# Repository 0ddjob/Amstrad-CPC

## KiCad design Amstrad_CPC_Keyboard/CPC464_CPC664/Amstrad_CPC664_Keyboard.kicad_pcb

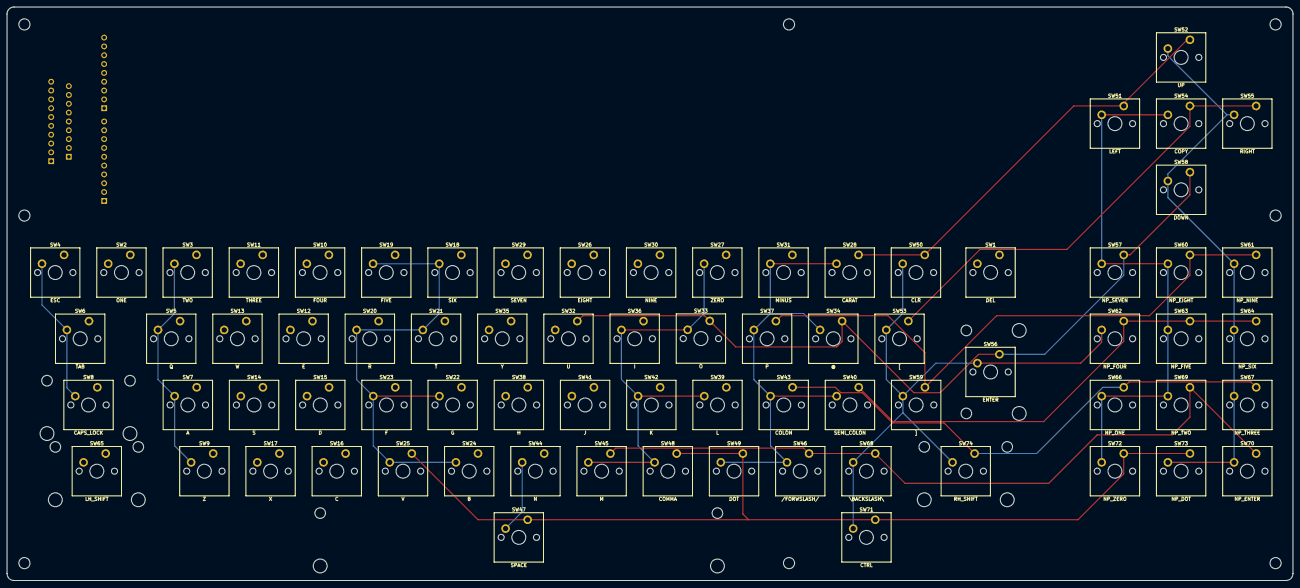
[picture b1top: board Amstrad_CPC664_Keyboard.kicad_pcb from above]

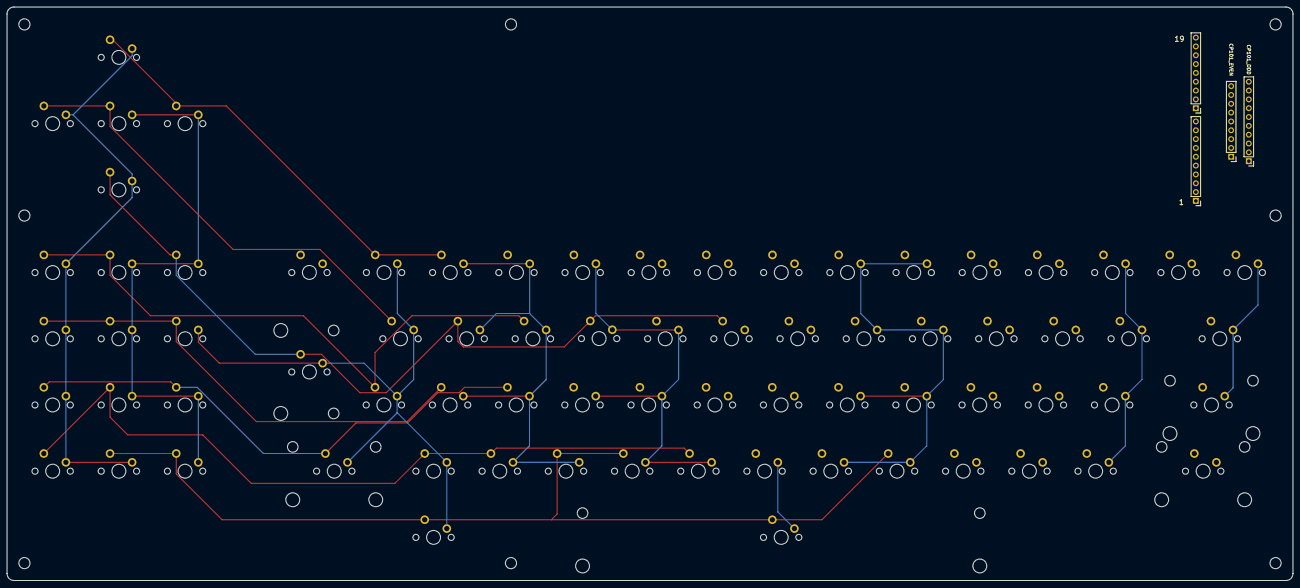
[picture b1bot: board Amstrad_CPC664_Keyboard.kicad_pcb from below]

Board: 2 copper layers, 370.0 x 165.0 mm, 91 parts (4 on the bottom side), 19 nets.

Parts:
H1, H2, H3, H4, H5, H6, H7, H8: MountingHole; MountingHole_3.2mm_M3
J1: CP101_ODD; PinHeader_1x10_P2.54mm_Vertical
J2: CP101_EVEN; PinHeader_1x09_P2.54mm_Vertical
J3: CP102_A; PinHeader_1x10_P2.54mm_Vertical
J4: CP102_B; PinHeader_1x09_P2.54mm_Vertical
KB8: CAPS_LOCK; Stabilizer_Cherry_MX_2.00u
KB47: SPACE; Stabilizer_Cherry_MX_7.00u
KB56: ENTER; Stabilizer_Cherry_MX_2.00u
KB65: LH_SHIFT; Stabilizer_Cherry_MX_2.00u
KB74: RH_SHIFT; Stabilizer_Cherry_MX_2.00u
SW1: DEL; SW_Cherry_MX_PCB_1.25u
SW2: ONE; SW_Cherry_MX_PCB_1.00u
SW3: TWO; SW_Cherry_MX_PCB_1.00u
SW4: ESC; SW_Cherry_MX_PCB_1.00u
SW5: Q; SW_Cherry_MX_PCB_1.00u
SW6: TAB; SW_Cherry_MX_PCB_1.75u
SW7: A; SW_Cherry_MX_PCB_1.00u
SW8: CAPS_LOCK; SW_Cherry_MX_PCB_2.00u
SW9: Z; SW_Cherry_MX_PCB_1.00u
SW10: FOUR; SW_Cherry_MX_PCB_1.00u
SW11: THREE; SW_Cherry_MX_PCB_1.00u
SW12: E; SW_Cherry_MX_PCB_1.00u
SW13: W; SW_Cherry_MX_PCB_1.00u
SW14: S; SW_Cherry_MX_PCB_1.00u
SW15: D; SW_Cherry_MX_PCB_1.00u
SW16: C; SW_Cherry_MX_PCB_1.00u
SW17: X; SW_Cherry_MX_PCB_1.00u
SW18: SIX; SW_Cherry_MX_PCB_1.00u
SW19: FIVE; SW_Cherry_MX_PCB_1.00u
SW20: R; SW_Cherry_MX_PCB_1.00u
SW21: T; SW_Cherry_MX_PCB_1.00u
SW22: G; SW_Cherry_MX_PCB_1.00u
SW23: F; SW_Cherry_MX_PCB_1.00u
SW24: B; SW_Cherry_MX_PCB_1.00u
SW25: V; SW_Cherry_MX_PCB_1.00u
SW26: EIGHT; SW_Cherry_MX_PCB_1.00u
SW27: ZERO; SW_Cherry_MX_PCB_1.00u
SW28: CARAT; SW_Cherry_MX_PCB_1.00u
SW29: SEVEN; SW_Cherry_MX_PCB_1.00u
SW30: NINE; SW_Cherry_MX_PCB_1.00u
SW31: MINUS; SW_Cherry_MX_PCB_1.00u
SW32: U; SW_Cherry_MX_PCB_1.00u
SW33: O; SW_Cherry_MX_PCB_1.00u
SW34: @; SW_Cherry_MX_PCB_1.00u
SW35: Y; SW_Cherry_MX_PCB_1.00u
SW36: I; SW_Cherry_MX_PCB_1.00u
SW37: P; SW_Cherry_MX_PCB_1.00u
SW38: H; SW_Cherry_MX_PCB_1.00u
SW39: L; SW_Cherry_MX_PCB_1.00u
SW40: SEMI_COLON; SW_Cherry_MX_PCB_1.00u
SW41: J; SW_Cherry_MX_PCB_1.00u
SW42: K; SW_Cherry_MX_PCB_1.00u
SW43: COLON; SW_Cherry_MX_PCB_1.00u
SW44: N; SW_Cherry_MX_PCB_1.00u
SW45: M; SW_Cherry_MX_PCB_1.00u
SW46: /FORWSLASH/; SW_Cherry_MX_PCB_1.00u
SW47: SPACE; SW_Cherry_MX_PCB_7.00u
SW48: COMMA; SW_Cherry_MX_PCB_1.00u
SW49: DOT; SW_Cherry_MX_PCB_1.00u
SW50: CLR; SW_Cherry_MX_PCB_1.00u
SW51: LEFT; SW_Cherry_MX_PCB_1.00u
SW52: UP; SW_Cherry_MX_PCB_1.00u
SW53: [; SW_Cherry_MX_PCB_1.00u
SW54: COPY; SW_Cherry_MX_PCB_1.00u
SW55: RIGHT; SW_Cherry_MX_PCB_1.00u
SW56: ENTER; SW_Cherry_MX_PCB_ISOEnter
SW57: NP_SEVEN; SW_Cherry_MX_PCB_1.00u
SW58: DOWN; SW_Cherry_MX_PCB_1.00u
SW59: ]; SW_Cherry_MX_PCB_1.00u
SW60: NP_EIGHT; SW_Cherry_MX_PCB_1.00u
SW61: NP_NINE; SW_Cherry_MX_PCB_1.00u
SW62: NP_FOUR; SW_Cherry_MX_PCB_1.00u
SW63: NP_FIVE; SW_Cherry_MX_PCB_1.00u
SW64: NP_SIX; SW_Cherry_MX_PCB_1.00u
SW65: LH_SHIFT; SW_Cherry_MX_PCB_2.25u
SW66: NP_ONE; SW_Cherry_MX_PCB_1.00u
SW67: NP_THREE; SW_Cherry_MX_PCB_1.00u
SW68: \BACKSLASH\; SW_Cherry_MX_PCB_1.00u
SW69: NP_TWO; SW_Cherry_MX_PCB_1.00u
SW70: NP_ENTER; SW_Cherry_MX_PCB_1.00u
SW71: CTRL; SW_Cherry_MX_PCB_1.00u
SW72: NP_ZERO; SW_Cherry_MX_PCB_1.00u
SW73: NP_DOT; SW_Cherry_MX_PCB_1.00u
SW74: RH_SHIFT; SW_Cherry_MX_PCB_2.00u

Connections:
KB_1: J1.1, J3.1, SW1.1
KB_2: J2.1, J3.2, SW1.2
KB_3: J1.2, J3.3, SW2.2, SW10.2, SW18.2, SW26.2, SW27.2, SW28.2, SW50.2, SW51.2, SW52.2
KB_4: J2.2, J3.4, SW3.2, SW11.2, SW19.2, SW29.2, SW30.2, SW31.2, SW53.2, SW54.2, SW55.2
KB_5: J1.3, J3.5, SW4.2, SW12.2, SW20.2, SW32.2, SW33.2, SW34.2, SW56.2, SW57.2, SW58.2
KB_6: J2.3, J3.6, SW5.2, SW13.2, SW21.2, SW35.2, SW36.2, SW37.2, SW59.2, SW60.2, SW61.2
KB_7: J1.4, J3.7, SW6.2, SW14.2, SW22.2, SW38.2, SW39.2, SW40.2, SW62.2, SW63.2, SW64.2
KB_8: J2.4, J3.8, SW7.2, SW15.2, SW23.2, SW41.2, SW42.2, SW43.2, SW65.2, SW66.2, SW67.2, SW74.2
KB_9: J1.5, J3.9, SW8.2, SW16.2, SW24.2, SW44.2, SW45.2, SW46.2, SW68.2, SW69.2, SW70.2
KB_10: J2.5, J3.10, SW9.2, SW17.2, SW25.2, SW47.2, SW48.2, SW49.2, SW71.2, SW72.2, SW73.2
KB_11: J1.6, SW2.1, SW3.1, SW4.1, SW5.1, SW6.1, SW7.1, SW8.1, SW9.1
KB_12: J2.6, SW10.1, SW11.1, SW12.1, SW13.1, SW14.1, SW15.1, SW16.1, SW17.1
KB_13: J1.7, SW18.1, SW19.1, SW20.1, SW21.1, SW22.1, SW23.1, SW24.1, SW25.1
KB_14: J2.7, SW26.1, SW29.1, SW32.1, SW35.1, SW38.1, SW41.1, SW44.1, SW47.1
KB_15: J1.8, SW27.1, SW30.1, SW33.1, SW36.1, SW39.1, SW42.1, SW45.1, SW48.1
KB_16: J2.8, SW28.1, SW31.1, SW34.1, SW37.1, SW40.1, SW43.1, SW46.1, SW49.1
KB_17: J1.9, SW50.1, SW53.1, SW56.1, SW59.1, SW62.1, SW65.1, SW68.1, SW71.1, SW74.1
KB_18: J2.9, SW51.1, SW54.1, SW57.1, SW60.1, SW63.1, SW66.1, SW69.1, SW72.1
KB_19: J1.10, SW52.1, SW55.1, SW58.1, SW61.1, SW64.1, SW67.1, SW70.1, SW73.1

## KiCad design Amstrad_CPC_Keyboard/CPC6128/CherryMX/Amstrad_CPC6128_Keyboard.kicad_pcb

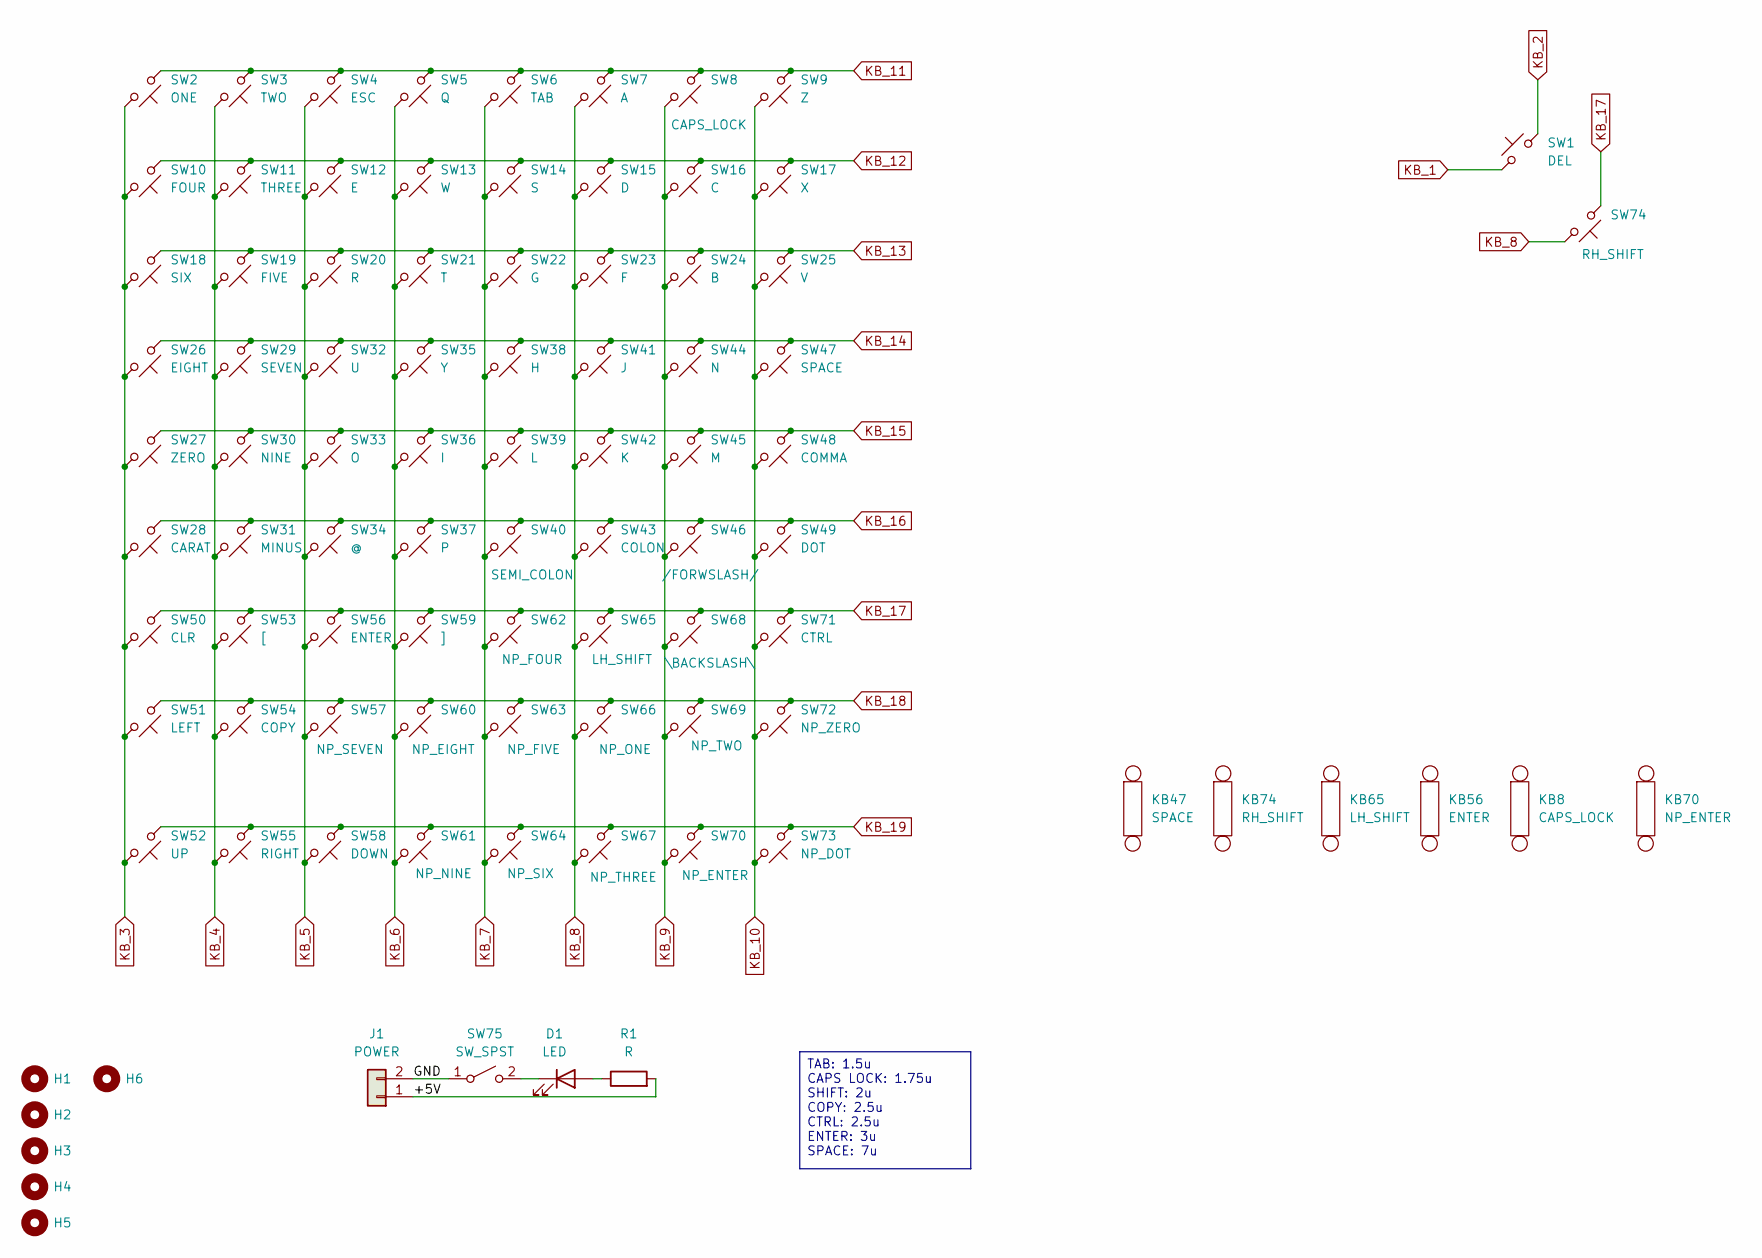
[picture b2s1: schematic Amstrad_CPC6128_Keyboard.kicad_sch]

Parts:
D1: LED; LED_D5.0mm
H1, H2, H3, H4, H5, H6: MountingHole; MountingHole_3.2mm_M3
J1: POWER; PinHeader_1x02_P2.54mm_Vertical
KB8: CAPS_LOCK; Stabilizer_Cherry_MX_2.00u
KB47: SPACE; Stabilizer_Cherry_MX_7.00u
KB56: ENTER; Stabilizer_Cherry_MX_2.00u
KB65: LH_SHIFT; Stabilizer_Cherry_MX_2.00u
KB70: NP_ENTER; Stabilizer_Cherry_MX_3.00u
KB74: RH_SHIFT; Stabilizer_Cherry_MX_2.00u
R1: R; R_Axial_DIN0207_L6.3mm_D2.5mm_P10.16mm_Horizontal
SW1: DEL; SW_Cherry_MX_PCB_1.00u
SW2: ONE; SW_Cherry_MX_PCB_1.00u
SW3: TWO; SW_Cherry_MX_PCB_1.00u
SW4: ESC; SW_Cherry_MX_PCB_1.00u
SW5: Q; SW_Cherry_MX_PCB_1.00u
SW6: TAB; SW_Cherry_MX_PCB_1.50u
SW7: A; SW_Cherry_MX_PCB_1.00u
SW8: CAPS_LOCK; SW_Cherry_MX_PCB_1.75u
SW9: Z; SW_Cherry_MX_PCB_1.00u
SW10: FOUR; SW_Cherry_MX_PCB_1.00u
SW11: THREE; SW_Cherry_MX_PCB_1.00u
SW12: E; SW_Cherry_MX_PCB_1.00u
SW13: W; SW_Cherry_MX_PCB_1.00u
SW14: S; SW_Cherry_MX_PCB_1.00u
SW15: D; SW_Cherry_MX_PCB_1.00u
SW16: C; SW_Cherry_MX_PCB_1.00u
SW17: X; SW_Cherry_MX_PCB_1.00u
SW18: SIX; SW_Cherry_MX_PCB_1.00u
SW19: FIVE; SW_Cherry_MX_PCB_1.00u
SW20: R; SW_Cherry_MX_PCB_1.00u
SW21: T; SW_Cherry_MX_PCB_1.00u
SW22: G; SW_Cherry_MX_PCB_1.00u
SW23: F; SW_Cherry_MX_PCB_1.00u
SW24: B; SW_Cherry_MX_PCB_1.00u
SW25: V; SW_Cherry_MX_PCB_1.00u
SW26: EIGHT; SW_Cherry_MX_PCB_1.00u
SW27: ZERO; SW_Cherry_MX_PCB_1.00u
SW28: CARAT; SW_Cherry_MX_PCB_1.00u
SW29: SEVEN; SW_Cherry_MX_PCB_1.00u
SW30: NINE; SW_Cherry_MX_PCB_1.00u
SW31: MINUS; SW_Cherry_MX_PCB_1.00u
SW32: U; SW_Cherry_MX_PCB_1.00u
SW33: O; SW_Cherry_MX_PCB_1.00u
SW34: @; SW_Cherry_MX_PCB_1.00u
SW35: Y; SW_Cherry_MX_PCB_1.00u
SW36: I; SW_Cherry_MX_PCB_1.00u
SW37: P; SW_Cherry_MX_PCB_1.00u
SW38: H; SW_Cherry_MX_PCB_1.00u
SW39: L; SW_Cherry_MX_PCB_1.00u
SW40: SEMI_COLON; SW_Cherry_MX_PCB_1.00u
SW41: J; SW_Cherry_MX_PCB_1.00u
SW42: K; SW_Cherry_MX_PCB_1.00u
SW43: COLON; SW_Cherry_MX_PCB_1.00u
SW44: N; SW_Cherry_MX_PCB_1.00u
SW45: M; SW_Cherry_MX_PCB_1.00u
SW46: /FORWSLASH/; SW_Cherry_MX_PCB_1.00u
SW47: SPACE; SW_Cherry_MX_PCB_7.00u
SW48: COMMA; SW_Cherry_MX_PCB_1.00u
SW49: DOT; SW_Cherry_MX_PCB_1.00u
SW50: CLR; SW_Cherry_MX_PCB_1.00u
SW51: LEFT; SW_Cherry_MX_PCB_1.00u
SW52: UP; SW_Cherry_MX_PCB_1.00u
SW53: [; SW_Cherry_MX_PCB_1.00u
SW54: COPY; SW_Cherry_MX_PCB_2.50u
SW55: RIGHT; SW_Cherry_MX_PCB_1.00u
SW56: ENTER; SW_Cherry_MX_PCB_ISOEnter
SW57: NP_SEVEN; SW_Cherry_MX_PCB_1.00u
SW58: DOWN; SW_Cherry_MX_PCB_1.00u
SW59: ]; SW_Cherry_MX_PCB_1.00u
SW60: NP_EIGHT; SW_Cherry_MX_PCB_1.00u
SW61: NP_NINE; SW_Cherry_MX_PCB_1.00u
SW62: NP_FOUR; SW_Cherry_MX_PCB_1.00u
SW63: NP_FIVE; SW_Cherry_MX_PCB_1.00u
SW64: NP_SIX; SW_Cherry_MX_PCB_1.00u
SW65: LH_SHIFT; SW_Cherry_MX_PCB_2.00u
SW66: NP_ONE; SW_Cherry_MX_PCB_1.00u
SW67: NP_THREE; SW_Cherry_MX_PCB_1.00u
SW68: \BACKSLASH\; SW_Cherry_MX_PCB_1.00u
SW69: NP_TWO; SW_Cherry_MX_PCB_1.00u
SW70: NP_ENTER; SW_Cherry_MX_PCB_3.00u
SW71: CTRL; SW_Cherry_MX_PCB_2.50u
SW72: NP_ZERO; SW_Cherry_MX_PCB_1.00u
SW73: NP_DOT; SW_Cherry_MX_PCB_1.00u
SW74: RH_SHIFT; SW_Cherry_MX_PCB_2.00u
SW75: SW_SPST; SW_Slide_SPDT_Straight_CK_OS102011MS2Q

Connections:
/+5V: J1.1, R1.2
/GND: J1.2, SW75.1 (A)
KB_1: SW1.1
KB_2: SW1.2
KB_3: SW2.2, SW10.2, SW18.2, SW26.2, SW27.2, SW28.2, SW50.2, SW51.2, SW52.2
KB_4: SW3.2, SW11.2, SW19.2, SW29.2, SW30.2, SW31.2, SW53.2, SW54.2, SW55.2
KB_5: SW4.2, SW12.2, SW20.2, SW32.2, SW33.2, SW34.2, SW56.2, SW57.2, SW58.2
KB_6: SW5.2, SW13.2, SW21.2, SW35.2, SW36.2, SW37.2, SW59.2, SW60.2, SW61.2
KB_7: SW6.2, SW14.2, SW22.2, SW38.2, SW39.2, SW40.2, SW62.2, SW63.2, SW64.2
KB_8: SW7.2, SW15.2, SW23.2, SW41.2, SW42.2, SW43.2, SW65.2, SW66.2, SW67.2, SW74.2
KB_9: SW8.2, SW16.2, SW24.2, SW44.2, SW45.2, SW46.2, SW68.2, SW69.2, SW70.2
KB_10: SW9.2, SW17.2, SW25.2, SW47.2, SW48.2, SW49.2, SW71.2, SW72.2, SW73.2
KB_11: SW2.1, SW3.1, SW4.1, SW5.1, SW6.1, SW7.1, SW8.1, SW9.1
KB_12: SW10.1, SW11.1, SW12.1, SW13.1, SW14.1, SW15.1, SW16.1, SW17.1
KB_13: SW18.1, SW19.1, SW20.1, SW21.1, SW22.1, SW23.1, SW24.1, SW25.1
KB_14: SW26.1, SW29.1, SW32.1, SW35.1, SW38.1, SW41.1, SW44.1, SW47.1
KB_15: SW27.1, SW30.1, SW33.1, SW36.1, SW39.1, SW42.1, SW45.1, SW48.1
KB_16: SW28.1, SW31.1, SW34.1, SW37.1, SW40.1, SW43.1, SW46.1, SW49.1
KB_17: SW50.1, SW53.1, SW56.1, SW59.1, SW62.1, SW65.1, SW68.1, SW71.1, SW74.1
KB_18: SW51.1, SW54.1, SW57.1, SW60.1, SW63.1, SW66.1, SW69.1, SW72.1
KB_19: SW52.1, SW55.1, SW58.1, SW61.1, SW64.1, SW67.1, SW70.1, SW73.1
unnamed: D1.2 (A), R1.1
unnamed: D1.1 (K), SW75.2 (B)

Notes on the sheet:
TAB: 1.5u CAPS LOCK: 1.75u SHIFT: 2u COPY: 2.5u CTRL: 2.5u ENTER: 3u SPACE: 7u

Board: 2 copper layers, 85 parts (0 on the bottom side), 21 nets, no tracks yet.

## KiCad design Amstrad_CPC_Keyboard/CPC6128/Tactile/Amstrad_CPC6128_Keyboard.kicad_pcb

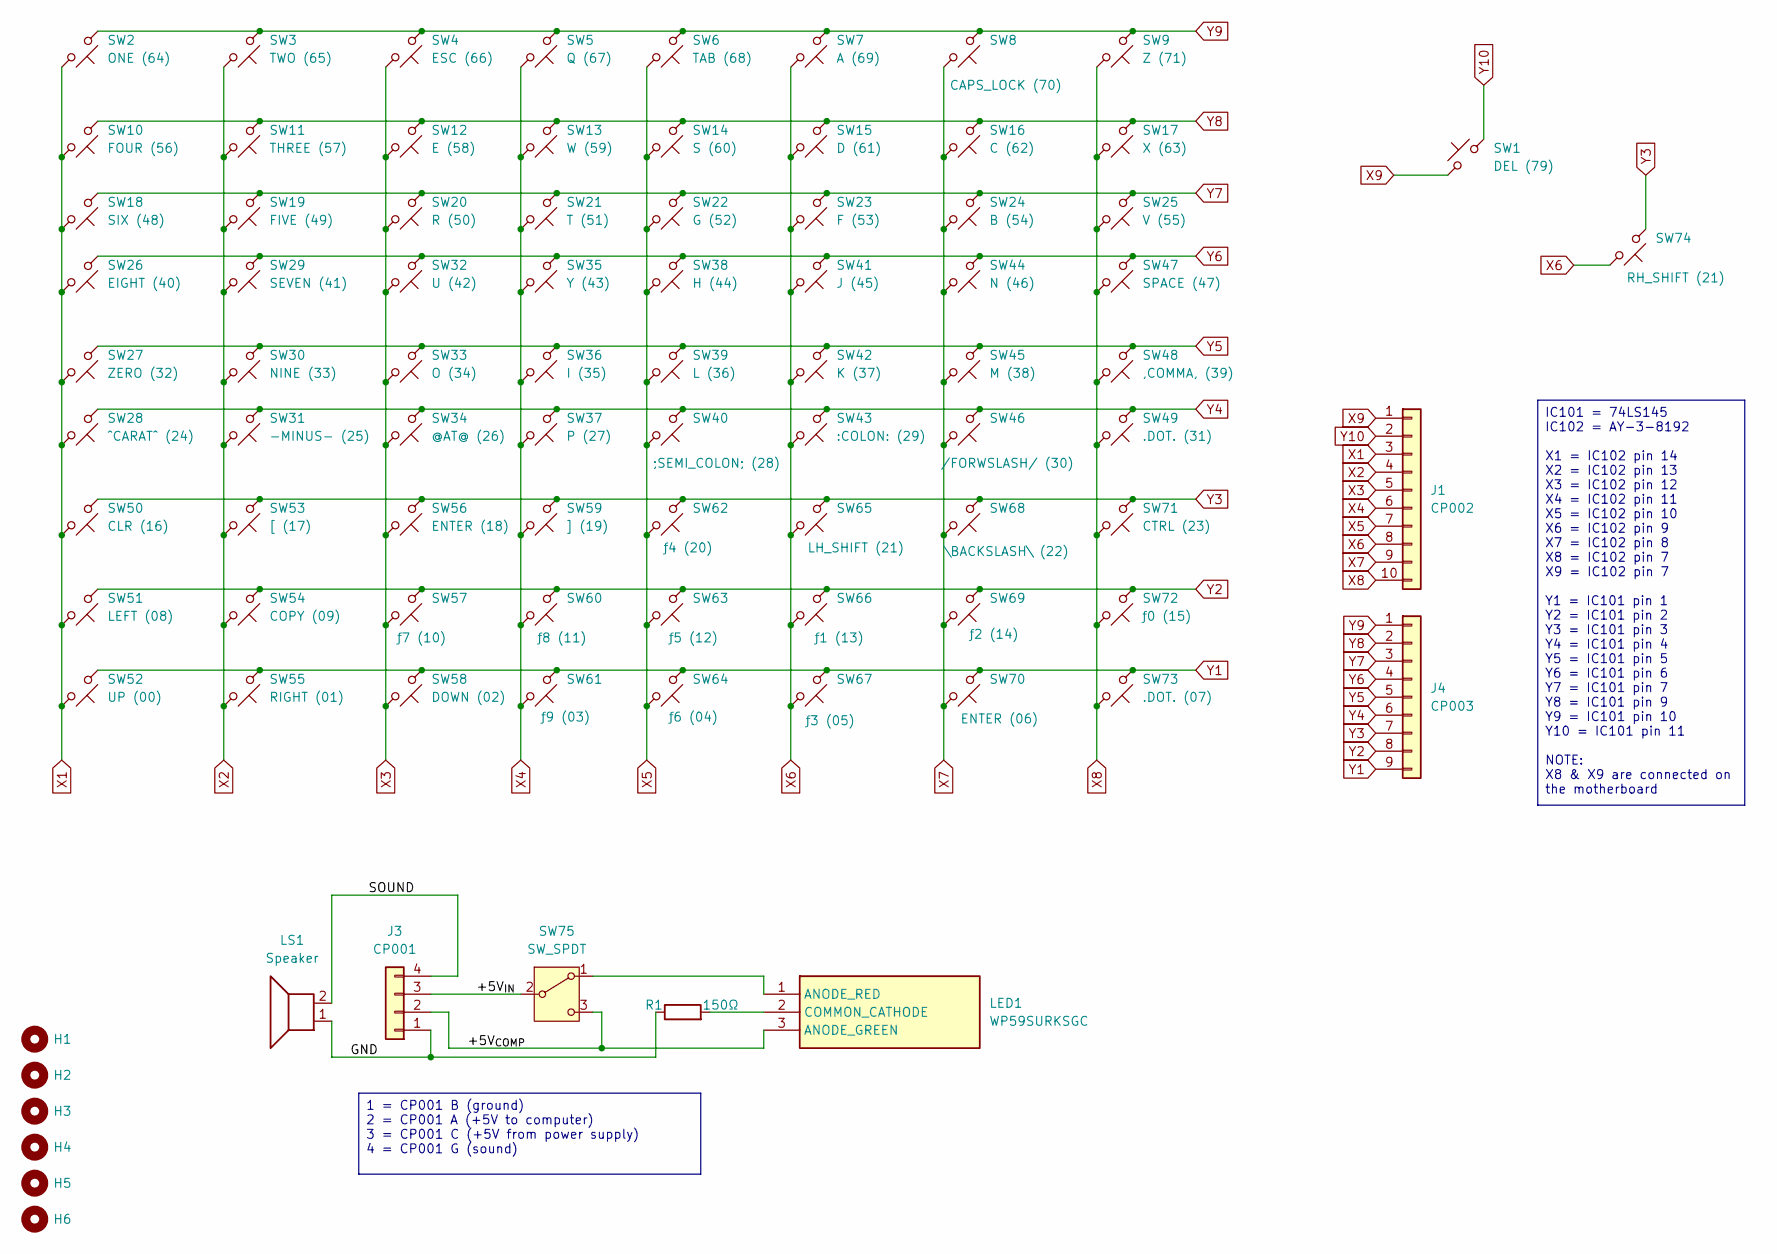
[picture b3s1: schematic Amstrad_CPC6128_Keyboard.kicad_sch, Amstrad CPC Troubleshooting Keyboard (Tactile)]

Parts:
H1, H2, H3, H4, H5, H6: MountingHole; MountingHole_3.2mm_M3
J1: CP002; PinHeader_1x10_P2.54mm_Vertical
J3: CP001; PinHeader_1x04_P2.54mm_Vertical
J4: CP003; PinHeader_1x09_P2.54mm_Vertical
LED1: WP59SURKSGC; WP59EGC; Mouser Part Number 604-WP59SURKSGC
LS1: Speaker; Buzzer_12x9.5RM7.6
R1: 150Ω; R_Axial_DIN0207_L6.3mm_D2.5mm_P10.16mm_Horizontal
SW1: DEL (79); SW_PUSH-12mm
SW2: ONE (64); SW_PUSH-12mm
SW3: TWO (65); SW_PUSH-12mm
SW4: ESC (66); SW_PUSH-12mm
SW5: Q (67); SW_PUSH-12mm
SW6: TAB (68); SW_PUSH-12mm
SW7: A (69); SW_PUSH-12mm
SW8: CAPS_LOCK (70); SW_PUSH-12mm
SW9: Z (71); SW_PUSH-12mm
SW10: FOUR (56); SW_PUSH-12mm
SW11: THREE (57); SW_PUSH-12mm
SW12: E (58); SW_PUSH-12mm
SW13: W (59); SW_PUSH-12mm
SW14: S (60); SW_PUSH-12mm
SW15: D (61); SW_PUSH-12mm
SW16: C (62); SW_PUSH-12mm
SW17: X (63); SW_PUSH-12mm
SW18: SIX (48); SW_PUSH-12mm
SW19: FIVE (49); SW_PUSH-12mm
SW20: R (50); SW_PUSH-12mm
SW21: T (51); SW_PUSH-12mm
SW22: G (52); SW_PUSH-12mm
SW23: F (53); SW_PUSH-12mm
SW24: B (54); SW_PUSH-12mm
SW25: V (55); SW_PUSH-12mm
SW26: EIGHT (40); SW_PUSH-12mm
SW27: ZERO (32); SW_PUSH-12mm
SW28: ^CARAT^ (24); SW_PUSH-12mm
SW29: SEVEN (41); SW_PUSH-12mm
SW30: NINE (33); SW_PUSH-12mm
SW31: -MINUS- (25); SW_PUSH-12mm
SW32: U (42); SW_PUSH-12mm
SW33: O (34); SW_PUSH-12mm
SW34: @AT@ (26); SW_PUSH-12mm
SW35: Y (43); SW_PUSH-12mm
SW36: I (35); SW_PUSH-12mm
SW37: P (27); SW_PUSH-12mm
SW38: H (44); SW_PUSH-12mm
SW39: L (36); SW_PUSH-12mm
SW40: ;SEMI_COLON; (28); SW_PUSH-12mm
SW41: J (45); SW_PUSH-12mm
SW42: K (37); SW_PUSH-12mm
SW43: :COLON: (29); SW_PUSH-12mm
SW44: N (46); SW_PUSH-12mm
SW45: M (38); SW_PUSH-12mm
SW46: /FORWSLASH/ (30); SW_PUSH-12mm
SW47: SPACE (47); SW_PUSH-12mm
SW48: ,COMMA, (39); SW_PUSH-12mm
SW49: .DOT. (31); SW_PUSH-12mm
SW50: CLR (16); SW_PUSH-12mm
SW51: LEFT (08); SW_PUSH-12mm
SW52: UP (00); SW_PUSH-12mm
SW53: [ (17); SW_PUSH-12mm
SW54: COPY (09); SW_PUSH-12mm
SW55: RIGHT (01); SW_PUSH-12mm
SW56: ENTER (18); SW_PUSH-12mm
SW57: ƒ7 (10); SW_PUSH-12mm
SW58: DOWN (02); SW_PUSH-12mm
SW59: ] (19); SW_PUSH-12mm
SW60: ƒ8 (11); SW_PUSH-12mm
SW61: ƒ9 (03); SW_PUSH-12mm
SW62: ƒ4 (20); SW_PUSH-12mm
SW63: ƒ5 (12); SW_PUSH-12mm
SW64: ƒ6 (04); SW_PUSH-12mm
SW65: LH_SHIFT (21); SW_PUSH-12mm
SW66: ƒ1 (13); SW_PUSH-12mm
SW67: ƒ3 (05); SW_PUSH-12mm
SW68: \BACKSLASH\ (22); SW_PUSH-12mm
SW69: ƒ2 (14); SW_PUSH-12mm
SW70: ENTER (06); SW_PUSH-12mm
SW71: CTRL (23); SW_PUSH-12mm
SW72: ƒ0 (15); SW_PUSH-12mm
SW73: .DOT. (07); SW_PUSH-12mm
SW74: RH_SHIFT (21); SW_PUSH-12mm
SW75: SW_SPDT; L102011MS02Q

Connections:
/+5V_{COMP}: J3.2, LED1.3 (ANODE_GREEN), SW75.3 (C)
/+5V_{IN}: J3.3, SW75.2 (B)
/GND: J3.1, LS1.1, R1.1
/SOUND: J3.4, LS1.2
unnamed: LED1.1 (ANODE_RED), SW75.1 (A)
unnamed: LED1.2 (COMMON_CATHODE), R1.2
X1: J1.3, SW2.2, SW10.2, SW18.2, SW26.2, SW27.2, SW28.2, SW50.2, SW51.2, SW52.2
X2: J1.4, SW3.2, SW11.2, SW19.2, SW29.2, SW30.2, SW31.2, SW53.2, SW54.2, SW55.2
X3: J1.5, SW4.2, SW12.2, SW20.2, SW32.2, SW33.2, SW34.2, SW56.2, SW57.2, SW58.2
X4: J1.6, SW5.2, SW13.2, SW21.2, SW35.2, SW36.2, SW37.2, SW59.2, SW60.2, SW61.2
X5: J1.7, SW6.2, SW14.2, SW22.2, SW38.2, SW39.2, SW40.2, SW62.2, SW63.2, SW64.2
X6: J1.8, SW7.2, SW15.2, SW23.2, SW41.2, SW42.2, SW43.2, SW65.2, SW66.2, SW67.2, SW74.2
X7: J1.9, SW8.2, SW16.2, SW24.2, SW44.2, SW45.2, SW46.2, SW68.2, SW69.2, SW70.2
X8: J1.10, SW9.2, SW17.2, SW25.2, SW47.2, SW48.2, SW49.2, SW71.2, SW72.2, SW73.2
X9: J1.1, SW1.1
Y1: J4.9, SW52.1, SW55.1, SW58.1, SW61.1, SW64.1, SW67.1, SW70.1, SW73.1
Y2: J4.8, SW51.1, SW54.1, SW57.1, SW60.1, SW63.1, SW66.1, SW69.1, SW72.1
Y3: J4.7, SW50.1, SW53.1, SW56.1, SW59.1, SW62.1, SW65.1, SW68.1, SW71.1, SW74.1
Y4: J4.6, SW28.1, SW31.1, SW34.1, SW37.1, SW40.1, SW43.1, SW46.1, SW49.1
Y5: J4.5, SW27.1, SW30.1, SW33.1, SW36.1, SW39.1, SW42.1, SW45.1, SW48.1
Y6: J4.4, SW26.1, SW29.1, SW32.1, SW35.1, SW38.1, SW41.1, SW44.1, SW47.1
Y7: J4.3, SW18.1, SW19.1, SW20.1, SW21.1, SW22.1, SW23.1, SW24.1, SW25.1
Y8: J4.2, SW10.1, SW11.1, SW12.1, SW13.1, SW14.1, SW15.1, SW16.1, SW17.1
Y9: J4.1, SW2.1, SW3.1, SW4.1, SW5.1, SW6.1, SW7.1, SW8.1, SW9.1
Y10: J1.2, SW1.2

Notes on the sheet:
1 = CP001 B (ground) 2 = CP001 A (+5V to computer) 3 = CP001 C (+5V from power supply) 4 = CP001 G (sound)
IC101 = 74LS145 IC102 = AY-3-8192 X1 = IC102 pin 14 X2 = IC102 pin 13 X3 = IC102 pin 12 X4 = IC102 pin 11 X5 = IC102 pin 10 X6 = IC102 pin 9 X7 = IC102 pin 8 X8 = IC102 pin 7 X9 = IC102 pin 7 Y1 = IC101 pin 1 Y2 = IC101 pin 2 Y3 = IC101 pin 3 Y4 = IC101 pin 4 Y5 = IC101 pin 5 Y6 = IC101 pin 6 Y7 = 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

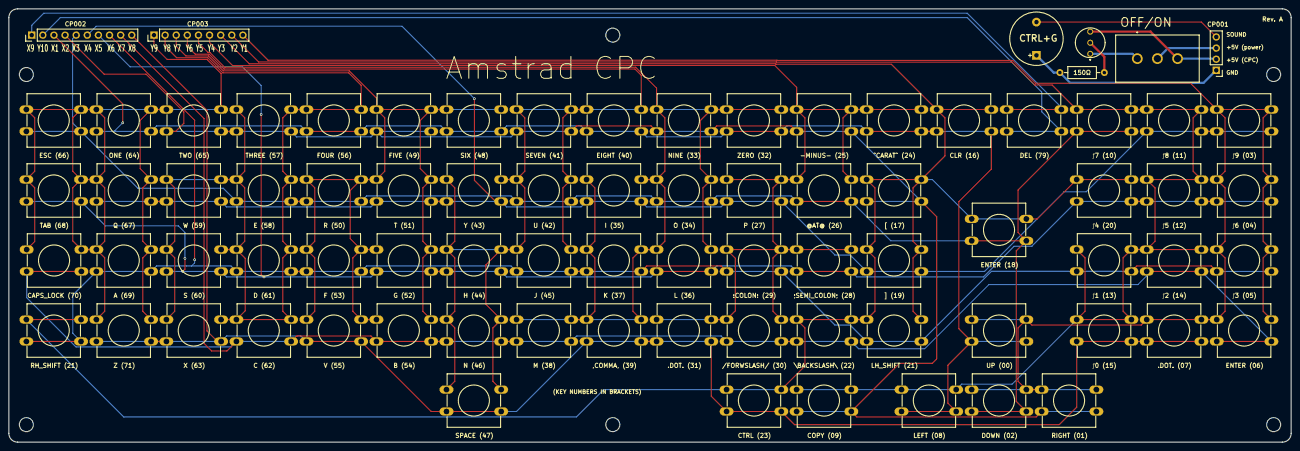
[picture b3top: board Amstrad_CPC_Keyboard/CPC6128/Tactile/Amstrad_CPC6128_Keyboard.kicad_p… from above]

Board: 2 copper layers, 293.0 x 99.0 mm, 87 parts (0 on the bottom side), 25 nets.

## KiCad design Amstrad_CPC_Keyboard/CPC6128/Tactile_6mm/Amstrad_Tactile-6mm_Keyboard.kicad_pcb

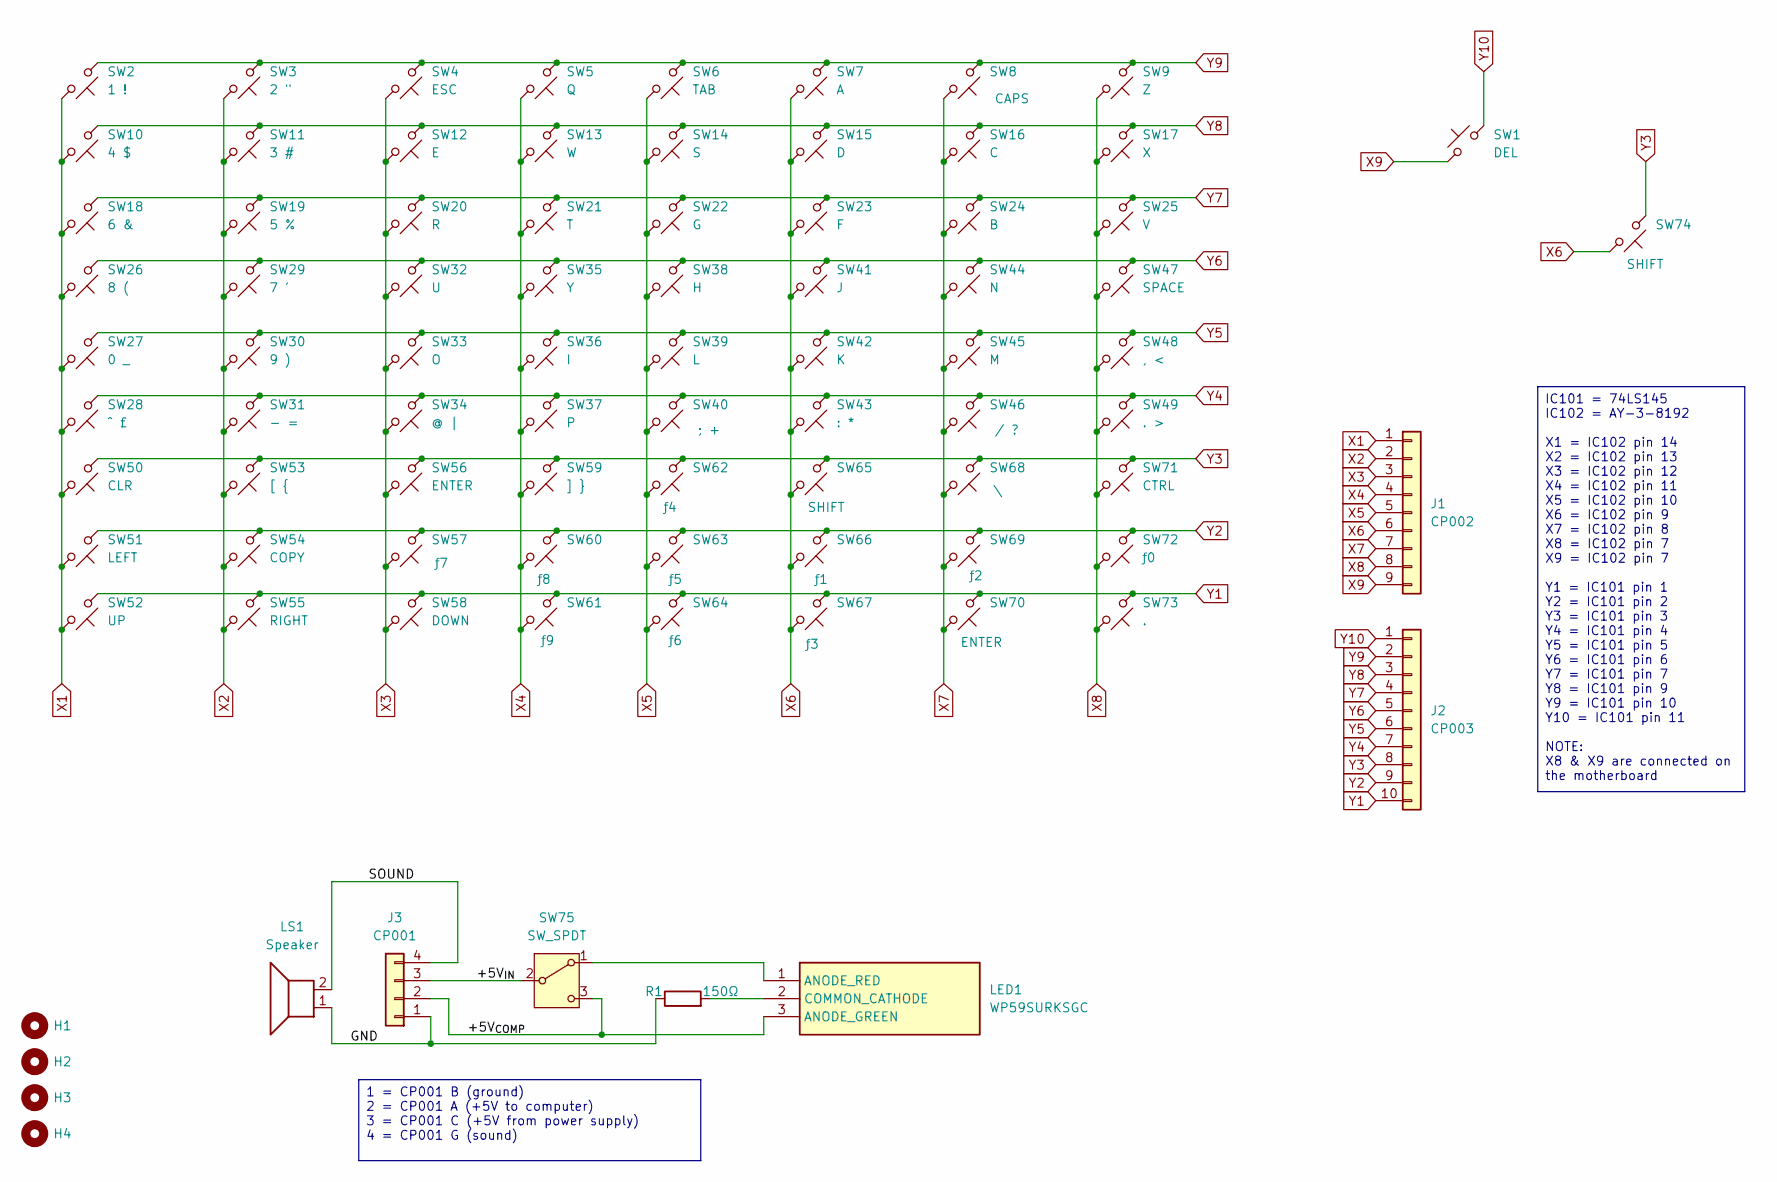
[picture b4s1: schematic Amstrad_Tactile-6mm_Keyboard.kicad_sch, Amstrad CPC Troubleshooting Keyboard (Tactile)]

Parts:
H1, H2, H3, H4: MountingHole; MountingHole_3.2mm_M3
J1: CP002; PinHeader_1x09_P2.54mm_Vertical
J2: CP003; PinHeader_1x10_P2.54mm_Vertical
J3: CP001; PinHeader_1x04_P2.54mm_Vertical
LED1: WP59SURKSGC; WP59EGC; Mouser Part Number 604-WP59SURKSGC
LS1: Speaker; Buzzer_12x9.5RM7.6
R1: 150Ω; R_Axial_DIN0207_L6.3mm_D2.5mm_P10.16mm_Horizontal
SW1: DEL; SW_PUSH_6mm
SW2: 1 !; SW_PUSH_6mm
SW3: 2 "; SW_PUSH_6mm
SW4: ESC; SW_PUSH_6mm
SW5: Q; SW_PUSH_6mm
SW6: TAB; SW_PUSH_6mm
SW7: A; SW_PUSH_6mm
SW8: CAPS; SW_PUSH_6mm
SW9: Z; SW_PUSH_6mm
SW10: 4 $; SW_PUSH_6mm
SW11: 3 #; SW_PUSH_6mm
SW12: E; SW_PUSH_6mm
SW13: W; SW_PUSH_6mm
SW14: S; SW_PUSH_6mm
SW15: D; SW_PUSH_6mm
SW16: C; SW_PUSH_6mm
SW17: X; SW_PUSH_6mm
SW18: 6 &; SW_PUSH_6mm
SW19: 5 %; SW_PUSH_6mm
SW20: R; SW_PUSH_6mm
SW21: T; SW_PUSH_6mm
SW22: G; SW_PUSH_6mm
SW23: F; SW_PUSH_6mm
SW24: B; SW_PUSH_6mm
SW25: V; SW_PUSH_6mm
SW26: 8 (; SW_PUSH_6mm
SW27: 0 _; SW_PUSH_6mm
SW28: ^ £; SW_PUSH_6mm
SW29: 7 '; SW_PUSH_6mm
SW30: 9 ); SW_PUSH_6mm
SW31: - =; SW_PUSH_6mm
SW32: U; SW_PUSH_6mm
SW33: O; SW_PUSH_6mm
SW34: @ |; SW_PUSH_6mm
SW35: Y; SW_PUSH_6mm
SW36: I; SW_PUSH_6mm
SW37: P; SW_PUSH_6mm
SW38: H; SW_PUSH_6mm
SW39: L; SW_PUSH_6mm
SW40: ; +; SW_PUSH_6mm
SW41: J; SW_PUSH_6mm
SW42: K; SW_PUSH_6mm
SW43: : *; SW_PUSH_6mm
SW44: N; SW_PUSH_6mm
SW45: M; SW_PUSH_6mm
SW46: / ?; SW_PUSH_6mm
SW47: SPACE; SW_PUSH_6mm
SW48: , <; SW_PUSH_6mm
SW49: . >; SW_PUSH_6mm
SW50: CLR; SW_PUSH_6mm
SW51: LEFT; SW_PUSH_6mm
SW52: UP; SW_PUSH_6mm
SW53: [ {; SW_PUSH_6mm
SW54: COPY; SW_PUSH_6mm
SW55: RIGHT; SW_PUSH_6mm
SW56, SW70: ENTER; SW_PUSH_6mm
SW57: ƒ7; SW_PUSH_6mm
SW58: DOWN; SW_PUSH_6mm
SW59: ] }; SW_PUSH_6mm
SW60: ƒ8; SW_PUSH_6mm
SW61: ƒ9; SW_PUSH_6mm
SW62: ƒ4; SW_PUSH_6mm
SW63: ƒ5; SW_PUSH_6mm
SW64: ƒ6; SW_PUSH_6mm
SW65, SW74: SHIFT; SW_PUSH_6mm
SW66: ƒ1; SW_PUSH_6mm
SW67: ƒ3; SW_PUSH_6mm
SW68: \; SW_PUSH_6mm
SW69: ƒ2; SW_PUSH_6mm
SW71: CTRL; SW_PUSH_6mm
SW72: ƒ0; SW_PUSH_6mm
SW73: .; SW_PUSH_6mm
SW75: SW_SPDT; L102011MS02Q

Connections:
/+5V_{COMP}: J3.2, LED1.3 (ANODE_GREEN), SW75.3 (C)
/+5V_{IN}: J3.3, SW75.2 (B)
/GND: J3.1, LS1.1, R1.1
/SOUND: J3.4, LS1.2
unnamed: LED1.1 (ANODE_RED), SW75.1 (A)
unnamed: LED1.2 (COMMON_CATHODE), R1.2
X1: J1.1, SW2.2, SW10.2, SW18.2, SW26.2, SW27.2, SW28.2, SW50.2, SW51.2, SW52.2
X2: J1.2, SW3.2, SW11.2, SW19.2, SW29.2, SW30.2, SW31.2, SW53.2, SW54.2, SW55.2
X3: J1.3, SW4.2, SW12.2, SW20.2, SW32.2, SW33.2, SW34.2, SW56.2, SW57.2, SW58.2
X4: J1.4, SW5.2, SW13.2, SW21.2, SW35.2, SW36.2, SW37.2, SW59.2, SW60.2, SW61.2
X5: J1.5, SW6.2, SW14.2, SW22.2, SW38.2, SW39.2, SW40.2, SW62.2, SW63.2, SW64.2
X6: J1.6, SW7.2, SW15.2, SW23.2, SW41.2, SW42.2, SW43.2, SW65.2, SW66.2, SW67.2, SW74.2
X7: J1.7, SW8.2, SW16.2, SW24.2, SW44.2, SW45.2, SW46.2, SW68.2, SW69.2, SW70.2
X8: J1.8, SW9.2, SW17.2, SW25.2, SW47.2, SW48.2, SW49.2, SW71.2, SW72.2, SW73.2
X9: J1.9, SW1.1
Y1: J2.10, SW52.1, SW55.1, SW58.1, SW61.1, SW64.1, SW67.1, SW70.1, SW73.1
Y2: J2.9, SW51.1, SW54.1, SW57.1, SW60.1, SW63.1, SW66.1, SW69.1, SW72.1
Y3: J2.8, SW50.1, SW53.1, SW56.1, SW59.1, SW62.1, SW65.1, SW68.1, SW71.1, SW74.1
Y4: J2.7, SW28.1, SW31.1, SW34.1, SW37.1, SW40.1, SW43.1, SW46.1, SW49.1
Y5: J2.6, SW27.1, SW30.1, SW33.1, SW36.1, SW39.1, SW42.1, SW45.1, SW48.1
Y6: J2.5, SW26.1, SW29.1, SW32.1, SW35.1, SW38.1, SW41.1, SW44.1, SW47.1
Y7: J2.4, SW18.1, SW19.1, SW20.1, SW21.1, SW22.1, SW23.1, SW24.1, SW25.1
Y8: J2.3, SW10.1, SW11.1, SW12.1, SW13.1, SW14.1, SW15.1, SW16.1, SW17.1
Y9: J2.2, SW2.1, SW3.1, SW4.1, SW5.1, SW6.1, SW7.1, SW8.1, SW9.1
Y10: J2.1, SW1.2

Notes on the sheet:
1 = CP001 B (ground) 2 = CP001 A (+5V to computer) 3 = CP001 C (+5V from power supply) 4 = CP001 G (sound)
IC101 = 74LS145 IC102 = AY-3-8192 X1 = IC102 pin 14 X2 = IC102 pin 13 X3 = IC102 pin 12 X4 = IC102 pin 11 X5 = IC102 pin 10 X6 = IC102 pin 9 X7 = IC102 pin 8 X8 = IC102 pin 7 X9 = IC102 pin 7 Y1 = IC101 pin 1 Y2 = IC101 pin 2 Y3 = IC101 pin 3 Y4 = IC101 pin 4 Y5 = IC101 pin 5 Y6 = IC101 pin 6 Y7 = 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

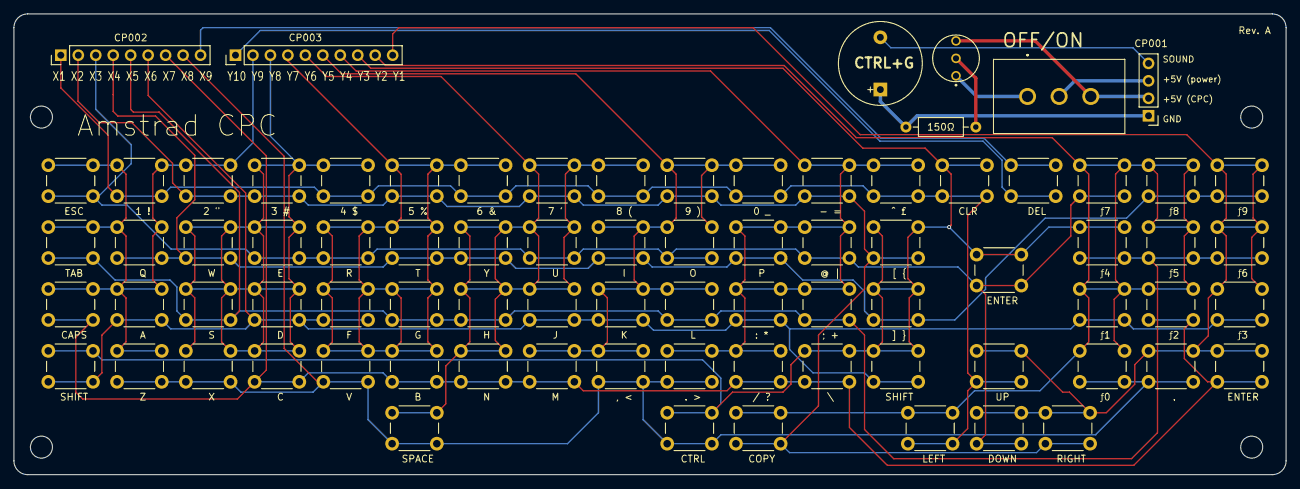
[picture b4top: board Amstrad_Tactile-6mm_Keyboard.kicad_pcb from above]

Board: 2 copper layers, 185.0 x 67.0 mm, 85 parts (0 on the bottom side), 25 nets.

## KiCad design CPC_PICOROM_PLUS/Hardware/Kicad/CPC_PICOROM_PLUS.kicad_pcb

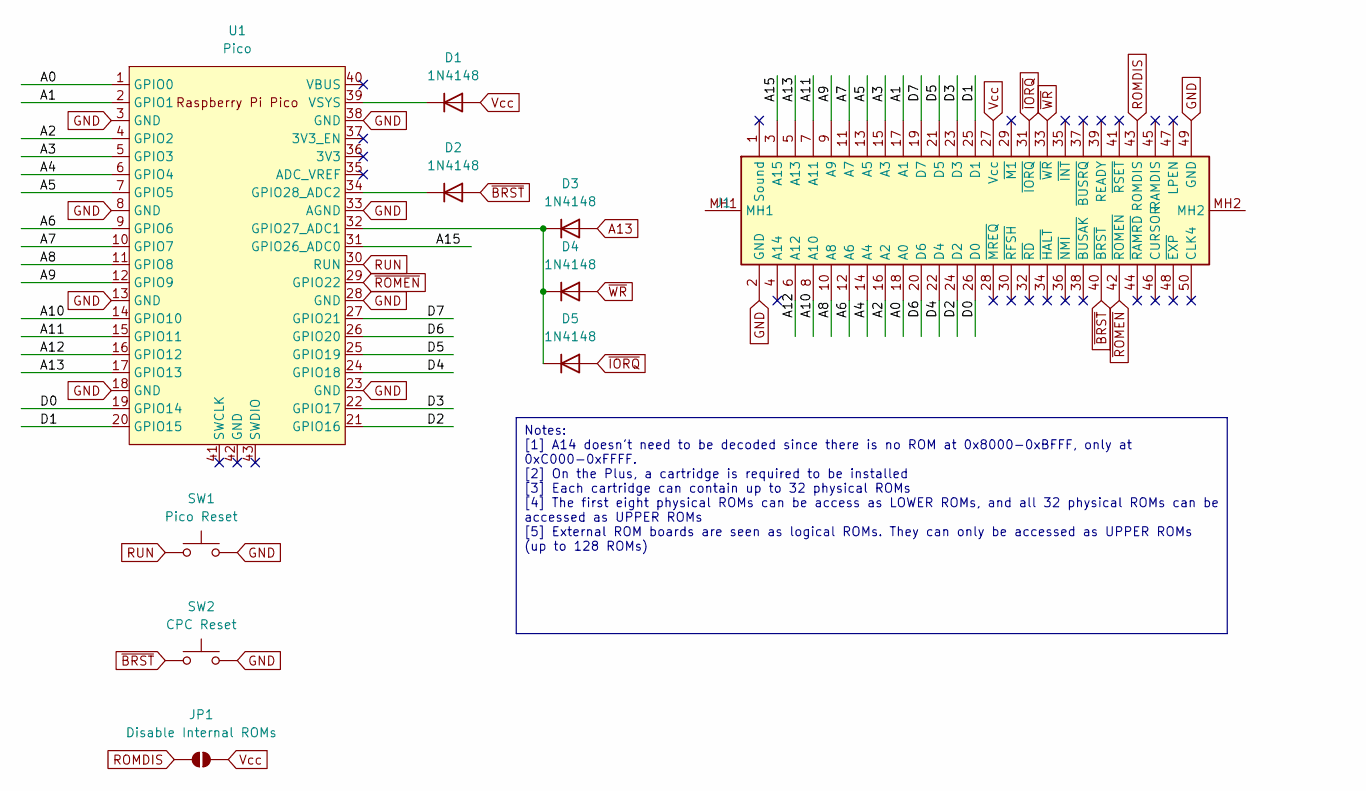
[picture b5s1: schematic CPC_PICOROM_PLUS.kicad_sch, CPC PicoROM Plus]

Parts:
D1, D2, D3, D4, D5: 1N4148; D_DO-35_SOD27_P7.62mm_Horizontal
J1: Amstrad_CPC_Plus_Expansion; 111050113L001_Amstrad_Plus; Manufacturer_Part_Number 111-050-113L001
JP1: Disable Internal ROMs; SolderJumper-2_P1.3mm_Open_RoundedPad1.0x1.5mm
SW1: Pico Reset; Switch_Tactile_6mm
SW2: CPC Reset; Switch_Tactile_6mm
U1: Pico; RPi_Pico_SMD_TH

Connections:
/A0: J1.18 (A0), U1.1 (GPIO0)
/A1: J1.17 (A1), U1.2 (GPIO1)
/A2: J1.16 (A2), U1.4 (GPIO2)
/A3: J1.15 (A3), U1.5 (GPIO3)
/A4: J1.14 (A4), U1.6 (GPIO4)
/A5: J1.13 (A5), U1.7 (GPIO5)
/A6: J1.12 (A6), U1.9 (GPIO6)
/A7: J1.11 (A7), U1.10 (GPIO7)
/A8: J1.10 (A8), U1.11 (GPIO8)
/A9: J1.9 (A9), U1.12 (GPIO9)
/A10: J1.8 (A10), U1.14 (GPIO10)
/A11: J1.7 (A11), U1.15 (GPIO11)
/A12: J1.6 (A12), U1.16 (GPIO12)
/A15: J1.3 (A15), U1.31 (GPIO26_ADC0)
/D0: J1.26 (D0), U1.19 (GPIO14)
/D1: J1.25 (D1), U1.20 (GPIO15)
/D2: J1.24 (D2), U1.21 (GPIO16)
/D3: J1.23 (D3), U1.22 (GPIO17)
/D4: J1.22 (D4), U1.24 (GPIO18)
/D5: J1.21 (D5), U1.25 (GPIO19)
/D6: J1.20 (D6), U1.26 (GPIO20)
/D7: J1.19 (D7), U1.27 (GPIO21)
A13: D3.2 (A), J1.5 (A13), U1.17 (GPIO13)
GND: J1.2 (GND), J1.49 (GND), SW1.2, SW2.2, U1.3 (GND), U1.8 (GND), U1.13 (GND), U1.18 (GND), U1.23 (GND), U1.28 (GND), U1.33 (AGND), U1.38 (GND)
unnamed: D1.1 (K), U1.39 (VSYS)
unnamed: D2.1 (K), U1.34 (GPIO28_ADC2)
unnamed: D3.1 (K), D4.1 (K), D5.1 (K), U1.32 (GPIO27_ADC1)
ROMDIS: J1.43 (ROMDIS), JP1.1 (A)
RUN: SW1.1, U1.30 (RUN)
Vcc: D1.2 (A), J1.27 (Vcc), JP1.2 (B)
~BRST: D2.2 (A), J1.40 (~BRST), SW2.1
~IORQ: D5.2 (A), J1.31 (~IORQ)
~ROMEN: J1.42 (~ROMEN), U1.29 (GPIO22)
~WR: D4.2 (A), J1.33 (~WR)

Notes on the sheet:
Notes: [1] A14 doesn't need to be decoded since there is no ROM at 0x8000-0xBFFF, only at 0xC000-0xFFFF. [2] On the Plus, a cartridge is required to be installed [3] Each cartridge can contain up to 32 physical ROMs [4] The first eight physical ROMs can be access as LOWER ROMs, and all 32 physical 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
